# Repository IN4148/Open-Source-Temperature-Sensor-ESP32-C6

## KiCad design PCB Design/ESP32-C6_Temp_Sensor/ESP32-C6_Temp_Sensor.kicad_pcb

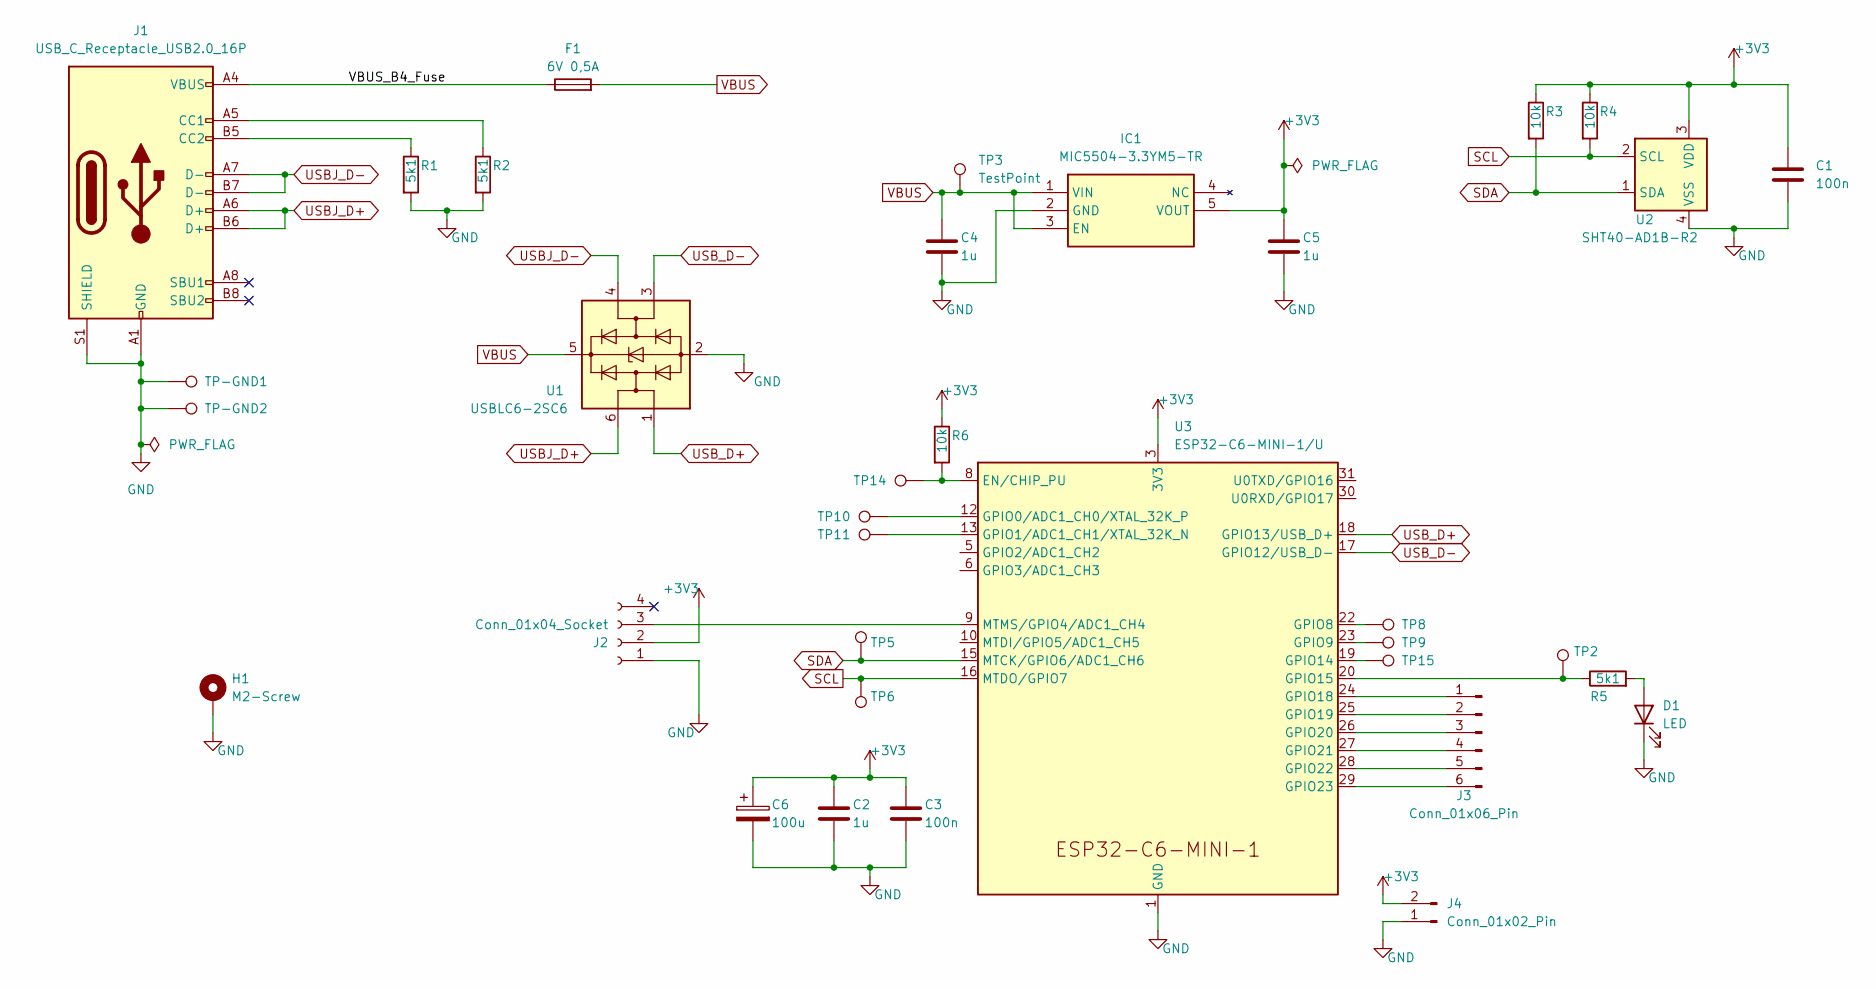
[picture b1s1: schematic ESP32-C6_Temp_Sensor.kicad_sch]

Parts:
C1, C3: 100n; C_0603_1608Metric_Pad1.08x0.95mm_HandSolder
C2, C4, C5: 1u; C_0603_1608Metric_Pad1.08x0.95mm_HandSolder
C6: 100u; CP_Elec_6.3x5.4
D1: LED; LED_0603_1608Metric_Pad1.05x0.95mm_HandSolder
F1: 6V 0,5A; Fuse_0603_1608Metric_Pad1.05x0.95mm_HandSolder; Mouser Part Number 603-SMD0603B050TF
H1: M2-Screw; MountingHole_2.2mm_M2_Pad
IC1: MIC5504-3.3YM5-TR; SOT95P280X145-5N; Mouser Part Number 998-MIC5504-3.3YM5TR
J1: USB_C_Receptacle_USB2.0_16P; USB_C_Receptacle_G-Switch_GT-USB-7010ASV
J2: Conn_01x04_Socket; PinHeader_1x04_P2.54mm_Vertical
J3: Conn_01x06_Pin; PinHeader_1x06_P2.54mm_Vertical
J4: Conn_01x02_Pin; PinHeader_1x02_P2.54mm_Vertical
R1, R2, R5: 5k1; R_0603_1608Metric_Pad0.98x0.95mm_HandSolder
R3, R4, R6: 10k; R_0603_1608Metric_Pad0.98x0.95mm_HandSolder
TP2, TP3, TP5, TP6, TP8, TP9, TP10, TP11, TP14, TP15: TestPoint; TestPoint_Pad_D1.0mm
TP-GND1, TP-GND2: GND_Point; TestPoint_Pad_2.0x2.0mm
U1: USBLC6-2SC6; SOT-23-6
U2: SHT40-AD1B-R2; Sensirion_DFN-4_1.5x1.5mm_P0.8mm_SHT4x_NoCentralPad
U3: ESP32-C6-MINI-1/U; ESP32-C6-MINI-1

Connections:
+3V3: C1.1, C2.1, C3.1, C5.1, C6.1, IC1.5 (VOUT), J2.2, J4.2, R3.1, R4.1, R6.1, U2.3 (VDD), U3.3 (3V3)
/VBUS_B4_Fuse: F1.1, J1.A4 (VBUS), J1.A9 (VBUS), J1.B4 (VBUS), J1.B9 (VBUS)
GND: C1.2, C2.2, C3.2, C4.2, C5.2, C6.2, D1.1 (K), H1.1, IC1.2 (GND), J1.A1 (GND), J1.A12 (GND), J1.B1 (GND), J1.B12 (GND), J1.S1 (SHIELD), J2.1, J4.1, R1.2, R2.2, TP-GND1.1, TP-GND2.1, U1.2 (GND), U2.4 (VSS), U3.1 (GND), U3.2 (GND), U3.11 (GND), U3.14 (GND), U3.36 (GND), U3.37 (GND), U3.38 (GND), U3.39 (GND), U3.40 (GND), U3.41 (GND), U3.42 (GND), U3.43 (GND), U3.44 (GND), U3.45 (GND), U3.46 (GND), U3.47 (GND), U3.48 (GND), U3.49 (GND), U3.50 (GND), U3.51 (GND), U3.52 (GND), U3.53 (GND)
unnamed: D1.2 (A), R5.2
unnamed: J1.A5 (CC1), R2.1
unnamed: J1.B5 (CC2), R1.1
unnamed: J2.3, U3.9 (MTMS/GPIO4/ADC1_CH4)
unnamed: J3.1, U3.24 (GPIO18)
unnamed: J3.2, U3.25 (GPIO19)
unnamed: J3.3, U3.26 (GPIO20)
unnamed: J3.4, U3.27 (GPIO21)
unnamed: J3.5, U3.28 (GPIO22)
unnamed: J3.6, U3.29 (GPIO23)
unnamed: R6.2, TP14.1, U3.8 (EN/CHIP_PU)
unnamed: TP10.1, U3.12 (GPIO0/ADC1_CH0/XTAL_32K_P)
unnamed: TP11.1, U3.13 (GPIO1/ADC1_CH1/XTAL_32K_N)
unnamed: TP8.1, U3.22 (GPIO8)
unnamed: TP9.1, U3.23 (GPIO9)
unnamed: TP15.1, U3.19 (GPIO14)
unnamed: R5.1, TP2.1, U3.20 (GPIO15)
SCL: R4.2, TP6.1, U2.2 (SCL), U3.16 (MTDO/GPIO7)
SDA: R3.2, TP5.1, U2.1 (SDA), U3.15 (MTCK/GPIO6/ADC1_CH6)
USBJ_D+: J1.A6 (D+), J1.B6 (D+), U1.6 (I/O1)
USBJ_D-: J1.A7 (D-), J1.B7 (D-), U1.4 (I/O2)
USB_D+: U1.1 (I/O1), U3.18 (GPIO13/USB_D+)
USB_D-: U1.3 (I/O2), U3.17 (GPIO12/USB_D-)
VBUS: C4.1, F1.2, IC1.1 (VIN), IC1.3 (EN), TP3.1, U1.5 (VBUS)

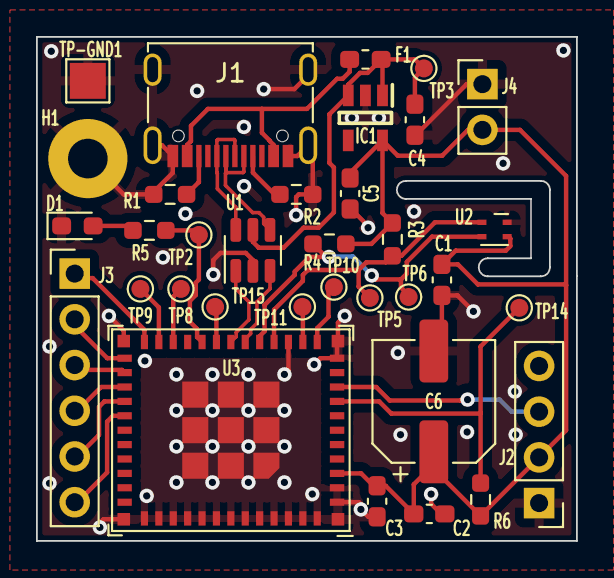
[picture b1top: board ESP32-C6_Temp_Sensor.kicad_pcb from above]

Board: 2 copper layers, 30.0 x 28.0 mm, 35 parts (1 on the bottom side), 27 nets.
